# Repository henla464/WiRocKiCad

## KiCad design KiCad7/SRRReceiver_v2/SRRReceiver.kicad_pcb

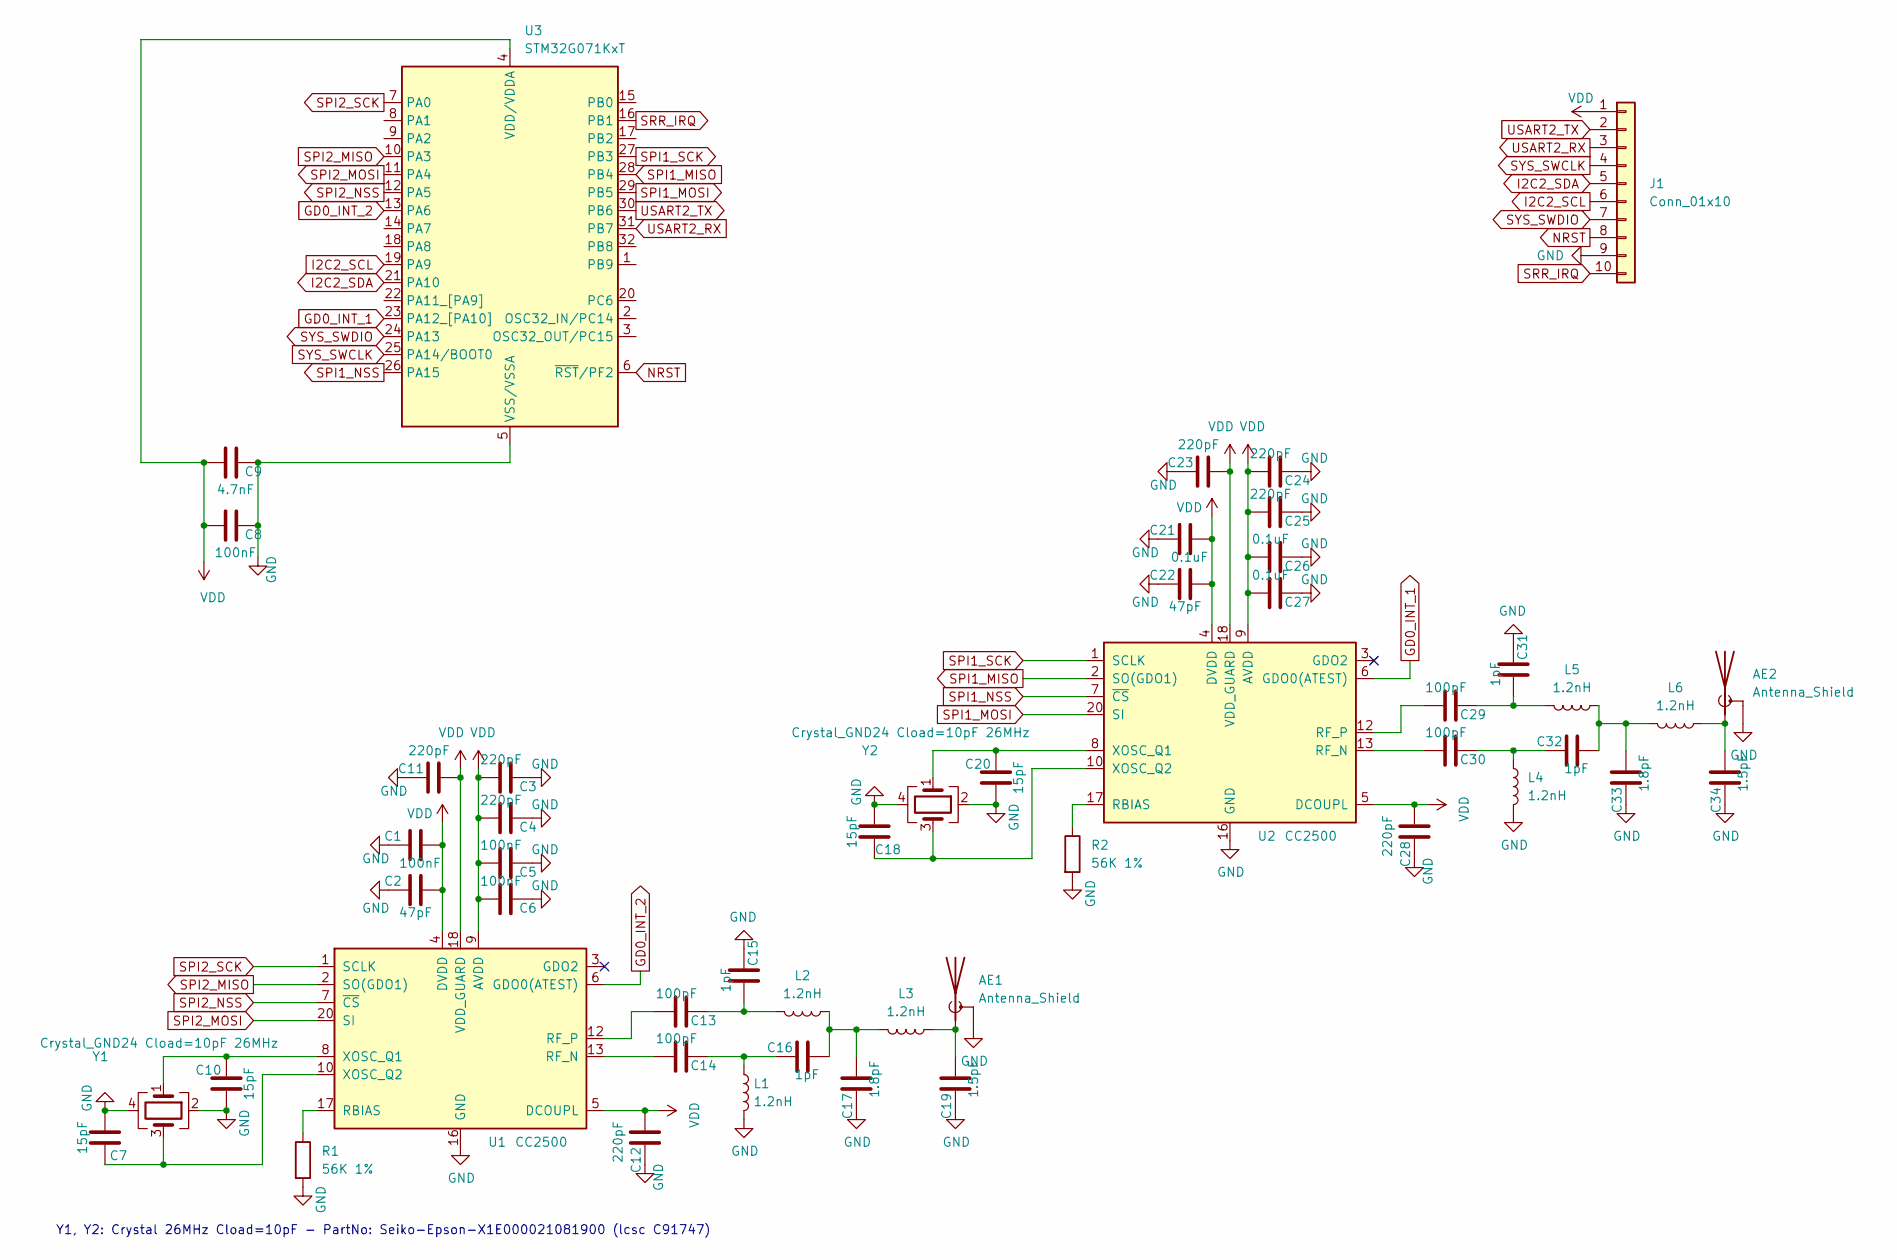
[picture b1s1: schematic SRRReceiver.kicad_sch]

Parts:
AE1, AE2: Antenna_Shield; Texas_SWRA117D_2.4GHz_Right
C1, C5, C6, C8: 100nF; C_0402_1005Metric; LCSC C1525
C2, C22: 47pF; C_0402_1005Metric; LCSC C1567
C3, C4, C11, C12, C23, C24, C25, C28: 220pF; C_0402_1005Metric; LCSC C16772
C7, C10, C18, C20: 15pF; C_0402_1005Metric; LCSC C1548
C9: 4.7nF; C_0402_1005Metric; LCSC C1538
C13, C14, C29, C30: 100pF; C_0402_1005Metric; LCSC C1546
C15, C16, C31, C32: 1pF; C_0402_1005Metric; LCSC C1550
C17, C33: 1.8pF; C_0402_1005Metric; LCSC C76902
C19, C34: 1.5pF; C_0402_1005Metric; LCSC C282238
C21, C26, C27: 0.1uF; C_0402_1005Metric; LCSC C1525
J1: Conn_01x10; FPC-Connector_1x10-1MP_P0.5mm_Horizontal
L1, L2, L3, L4, L5, L6: 1.2nH; L_0402_1005Metric; LCSC C77117
R1, R2: 56K 1%; R_0402_1005Metric; LCSC C25796
U1, U2: CC2500; Texas_S-PVQFN-N20_EP2.4x2.4mm; LCSC C57494
U3: STM32G071KxT; LQFP-32_7x7mm_P0.8mm
Y1, Y2: Crystal_GND24 Cload=10pF 26MHz; Crystal_SMD_3225-4Pin_3.2x2.5mm; LCSC C91747

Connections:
GD0_INT_1: U2.6 (GDO0(ATEST)), U3.23 (PA12_[PA10])
GD0_INT_2: U1.6 (GDO0(ATEST)), U3.13 (PA6)
GND: AE1.2 (Shield), AE2.2 (Shield), C1.1, C2.1, C3.1, C4.1, C5.1, C6.1, C7.1, C8.1, C9.1, C10.1, C11.1, C12.1, C15.1, C17.1, C18.1, C19.1, C20.1, C21.1, C22.1, C23.1, C24.1, C25.1, C26.1, C27.1, C28.1, C31.1, C33.1, C34.1, J1.9, L1.2, L4.2, R1.2, R2.2, U1.16 (GND), U1.19 (GND), U1.21 (GND), U2.16 (GND), U2.19 (GND), U2.21 (GND), U3.5 (VSS/VSSA), Y1.2, Y1.4, Y2.2, Y2.4
I2C2_SCL: J1.6, U3.19 (PA9)
I2C2_SDA: J1.5, U3.21 (PA10)
NRST: J1.8, U3.6 (~RST/PF2)
unnamed: AE1.1 (A), C19.2, L3.1
unnamed: AE2.1 (A), C34.2, L6.1
unnamed: C13.1, C15.2, L2.2
unnamed: C14.1, C16.1, L1.1
unnamed: C16.2, C17.2, L2.1, L3.2
unnamed: C29.1, C31.2, L5.2
unnamed: C30.1, C32.1, L4.1
unnamed: C32.2, C33.2, L5.1, L6.2
unnamed: R1.1, U1.17 (RBIAS)
unnamed: C14.2, U1.13 (RF_N)
unnamed: C13.2, U1.12 (RF_P)
unnamed: C10.2, U1.8 (XOSC_Q1), Y1.1
unnamed: C7.2, U1.10 (XOSC_Q2), Y1.3
unnamed: R2.1, U2.17 (RBIAS)
unnamed: C30.2, U2.13 (RF_N)
unnamed: C29.2, U2.12 (RF_P)
unnamed: C20.2, U2.8 (XOSC_Q1), Y2.1
unnamed: C18.2, U2.10 (XOSC_Q2), Y2.3
SPI1_MISO: U2.2 (SO(GDO1)), U3.28 (PB4)
SPI1_MOSI: U2.20 (SI), U3.29 (PB5)
SPI1_NSS: U2.7 (~CS), U3.26 (PA15)
SPI1_SCK: U2.1 (SCLK), U3.27 (PB3)
SPI2_MISO: U1.2 (SO(GDO1)), U3.10 (PA3)
SPI2_MOSI: U1.20 (SI), U3.11 (PA4)
SPI2_NSS: U1.7 (~CS), U3.12 (PA5)
SPI2_SCK: U1.1 (SCLK), U3.7 (PA0)
SRR_IRQ: J1.10, U3.16 (PB1)
SYS_SWCLK: J1.4, U3.25 (PA14/BOOT0)
SYS_SWDIO: J1.7, U3.24 (PA13)
USART2_RX: J1.3, U3.31 (PB7)
USART2_TX: J1.2, U3.30 (PB6)
VDD: C1.2, C2.2, C3.2, C4.2, C5.2, C6.2, C8.2, C9.2, C11.2, C12.2, C21.2, C22.2, C23.2, C24.2, C25.2, C26.2, C27.2, C28.2, J1.1, U1.4 (DVDD), U1.5 (DCOUPL), U1.9 (AVDD), U1.11 (AVDD), U1.14 (AVDD), U1.15 (AVDD), U1.18 (VDD_GUARD), U2.4 (DVDD), U2.5 (DCOUPL), U2.9 (AVDD), U2.11 (AVDD), U2.14 (AVDD), U2.15 (AVDD), U2.18 (VDD_GUARD), U3.4 (VDD/VDDA)

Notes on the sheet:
Y1, Y2: Crystal 26MHz Cload=10pF - PartNo: Seiko-Epson-X1E000021081900 (lcsc C91747)

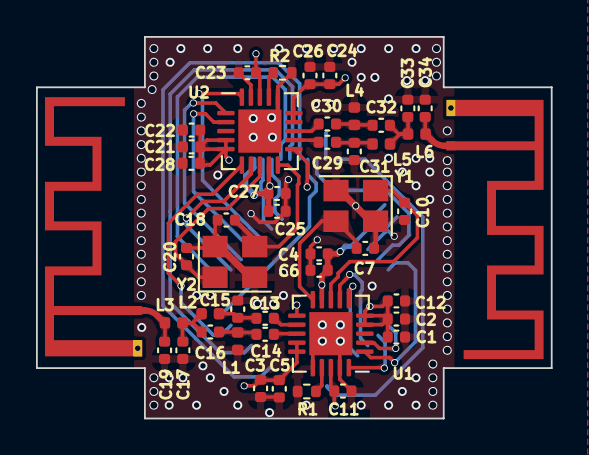
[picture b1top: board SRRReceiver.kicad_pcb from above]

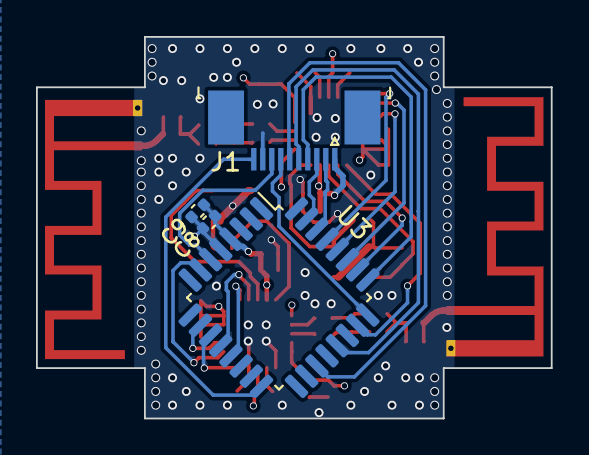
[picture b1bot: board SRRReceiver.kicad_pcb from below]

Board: 4 copper layers, 28.6 x 21.2 mm, 50 parts (4 on the bottom side), 38 nets.

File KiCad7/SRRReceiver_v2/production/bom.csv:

Designator,Footprint,Quantity,Value,LCSC Part #
"C1, C5, C6, C8",0402,4,100nF,C1525
"C10, C18, C20, C7",0402,4,15pF,C1548
"C11, C12, C23, C24, C25, C28, C3, C4",0402,8,220pF,C16772
"C13, C14, C29, C30",0402,4,100pF,C1546
"C15, C16, C31, C32",0402,4,1pF,C1550
"C17, C33",0402,2,1.8pF,C76902
"C19, C34",0402,2,1.5pF,C282238
"C2, C22",0402,2,47pF,C1567
"C21, C26, C27",0402,3,0.1uF,C1525
C9,0402,1,4.7nF,C1538
"L1, L2, L3, L4, L5, L6",0402,6,1.2nH,C77117
"R1, R2",0402,2,56K 1%,C25796
"U1, U2",Texas_S-PVQFN-N20_EP2.4x2.4mm,2,CC2500,C57494
"Y1, Y2",Crystal_SMD_3225-4Pin_3.2x2.5mm,2,Crystal_GND24 Cload=10pF 26MHz,C91747

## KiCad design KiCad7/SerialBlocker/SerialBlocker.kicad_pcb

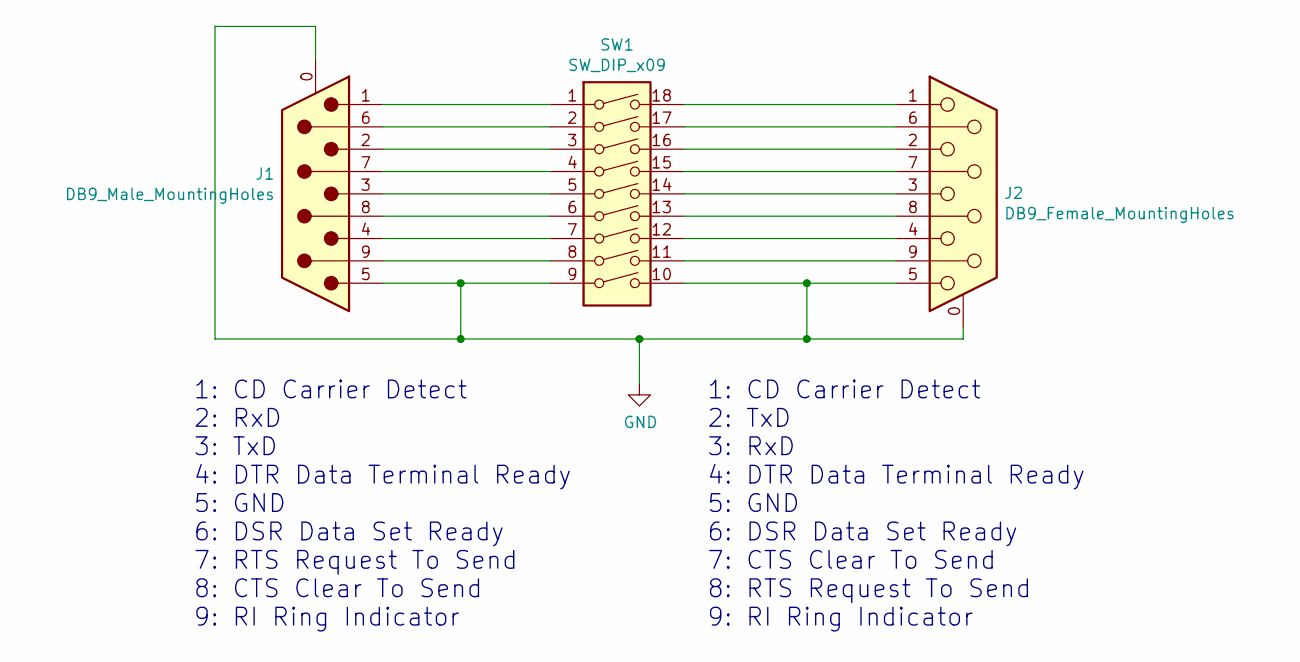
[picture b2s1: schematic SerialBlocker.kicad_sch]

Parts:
J1: DB9_Male_MountingHoles; DSUB-9_Male_Horizontal_P2.77x2.84mm_Edge_Housed_MountingHol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
J2: DB9_Female_MountingHoles; DSUB-9_Female_Horizontal_P2.77x2.84mm_Edge_offset6.96mm_cen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
SW1: SW_DIP_x09; PinHeader_Serial_Blocker

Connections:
GND: J1.0 (PAD), J1.5, J2.0 (PAD), J2.5, SW1.9, SW1.10
unnamed: J1.1, SW1.1
unnamed: J1.2, SW1.3
unnamed: J1.3, SW1.5
unnamed: J1.4, SW1.7
unnamed: J1.6, SW1.2
unnamed: J1.7, SW1.4
unnamed: J1.8, SW1.6
unnamed: J1.9, SW1.8
unnamed: J2.1, SW1.18
unnamed: J2.2, SW1.16
unnamed: J2.3, SW1.14
unnamed: J2.4, SW1.12
unnamed: J2.6, SW1.17
unnamed: J2.7, SW1.15
unnamed: J2.8, SW1.13
unnamed: J2.9, SW1.11

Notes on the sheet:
1: CD Carrier Detect 2: RxD 3: TxD 4: DTR Data Terminal Ready 5: GND 6: DSR Data Set Ready 7: RTS Request To Send 8: CTS Clear To Send 9: RI Ring Indicator
1: CD Carrier Detect 2: TxD 3: RxD 4: DTR Data Terminal Ready 5: GND 6: DSR Data Set Ready 7: CTS Clear To Send 8: RTS Request To Send 9: RI Ring Indicator

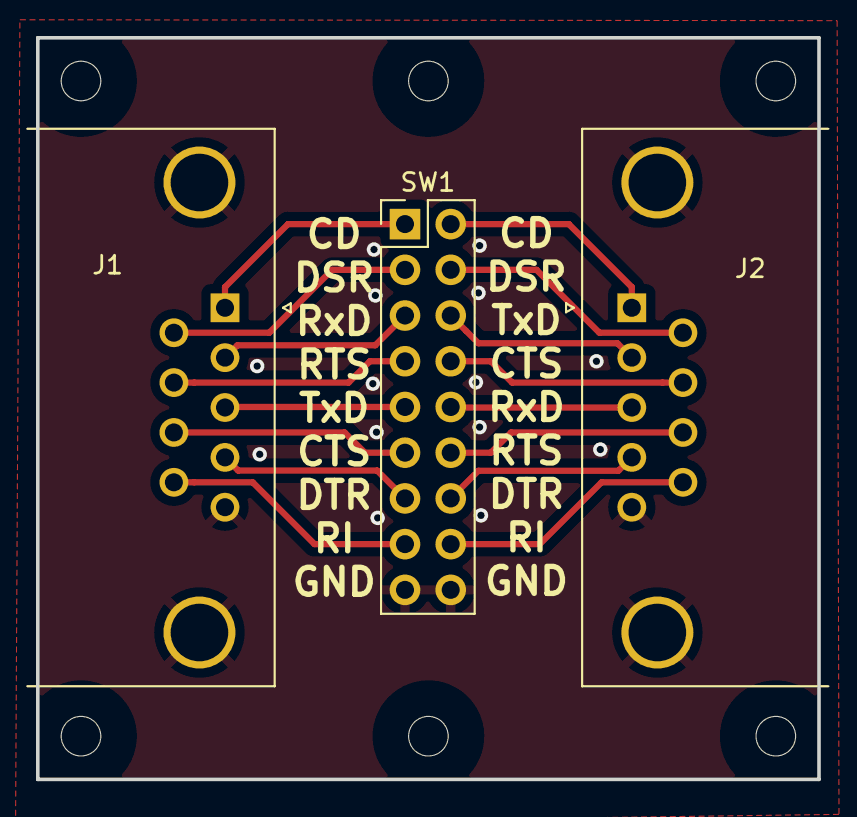
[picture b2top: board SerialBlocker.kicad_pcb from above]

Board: 2 copper layers, 43.4 x 41.2 mm, 3 parts (0 on the bottom side), 17 nets.

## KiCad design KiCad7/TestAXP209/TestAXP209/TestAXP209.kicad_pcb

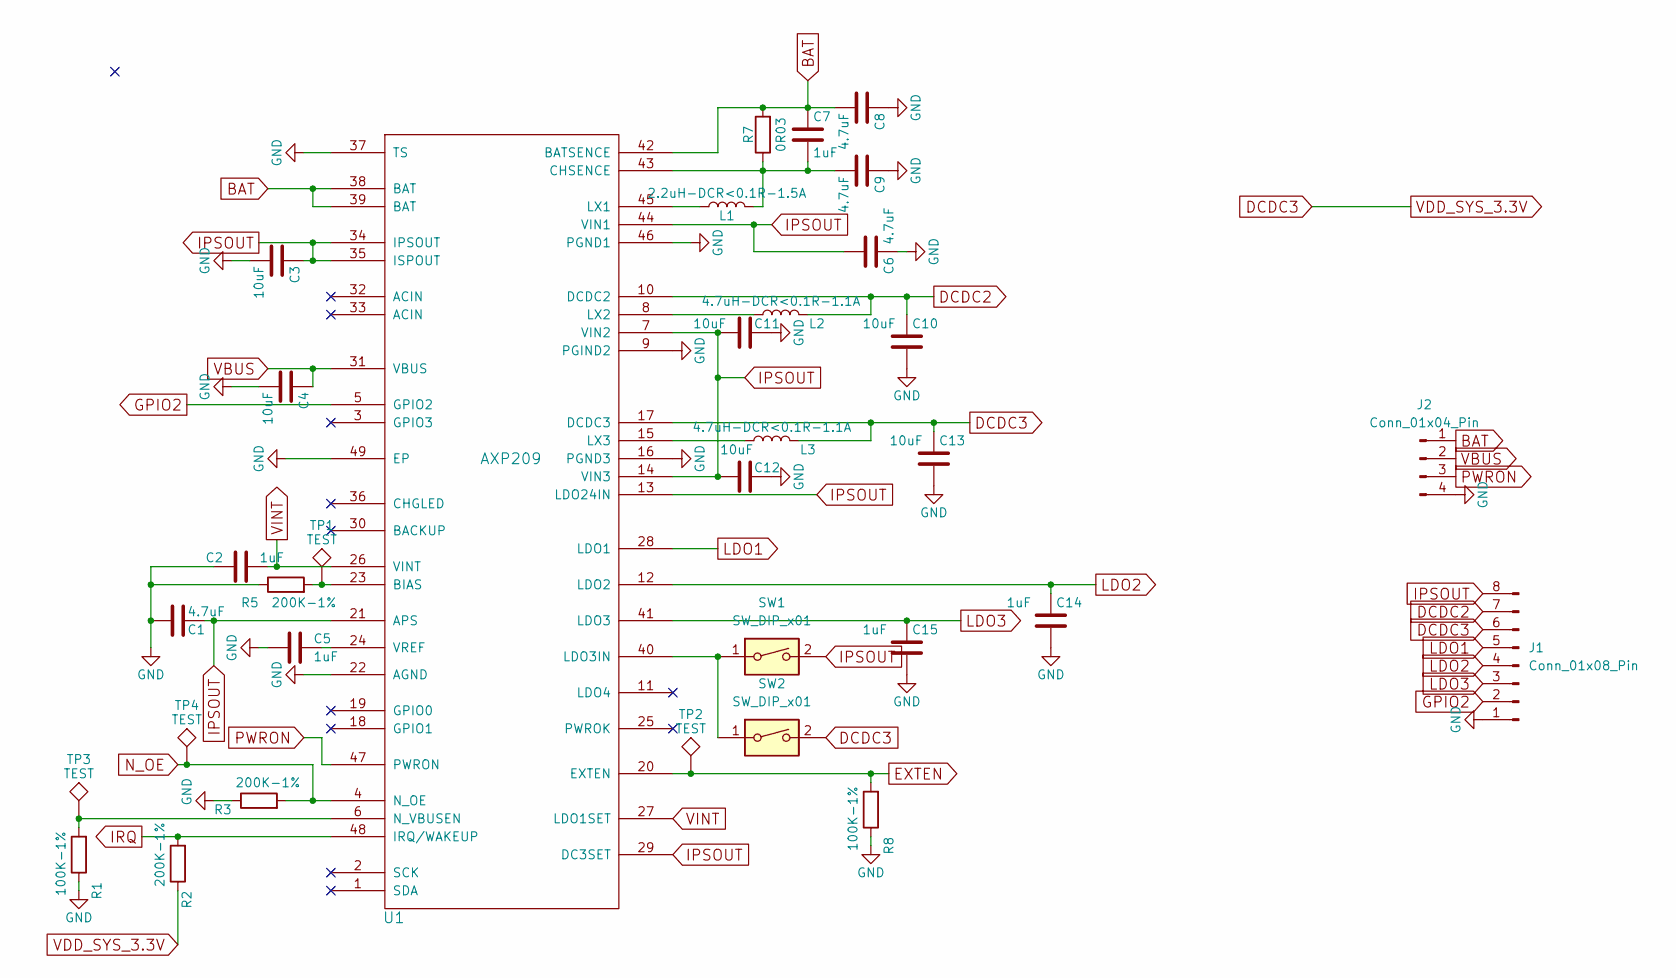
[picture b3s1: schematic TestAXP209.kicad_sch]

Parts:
C1, C6, C8, C9: 4.7uF; C_0603_1608Metric; ManufacturerPartNumber CL10A475KO8NNNC; LCSC Part # C19666
C2, C5, C7: 1uF; C_0603_1608Metric; ManufacturerPartNumber CL10A105KB8NNNC; LCSC Part # C15849
C3, C4: 10uF; C_0603_1608Metric; ManufacturerPartNumber CL10A106KP8NNNC; LCSC Part # C19702
C10, C11, C12, C13: 10uF; C_0603_1608Metric; ManufacturerPartNumber CL10A475KO8NNNC; LCSC Part # C19666
C14, C15: 1uF; C_0603_1608Metric; ManufacturerPartNumber CL10A475KO8NNNC; LCSC Part # C19666
J1: Conn_01x08_Pin; PinHeader_1x08_P2.54mm_Vertical
J2: Conn_01x04_Pin; PinHeader_1x04_P2.54mm_Vertical
L1: 2.2uH-DCR<0.1R-1.5A; Inductor_SLW4018; ManufacturerPartNumber SLW4018S2R2MST; LCSC Part # C206341
L2: 4.7uH-DCR<0.1R-1.1A; Inductor_SLW4018; ManufacturerPartNumber ?? DFE322520FD-4R7M=P2; LCSC Part # ?? C2045343
L3: 4.7uH-DCR<0.1R-1.1A; Inductor_SLW4018; ManufacturerPartNumber SWPA4030S4R7MT; LCSC Part # C57269
R1, R8: 100K-1%; R_0603_1608Metric; ManufacturerPartNumber 0603WAF1003T5E; LCSC Part # C25803
R2, R3, R5: 200K-1%; R_0603_1608Metric; ManufacturerPartNumber 0603WAF2003T5E; LCSC Part # C25811
R7: 0R03; R_0805_2012Metric; ManufacturerPartNumber 0805W4F300MT5E; LCSC Part # C247605
SW1, SW2: SW_DIP_x01; PinHeader_1x02_P2.54mm_Vertical
TP1, TP2, TP3, TP4: TEST; TestPoint_Pad_D1.0mm
U1: AXP209; qfn48_6x6mm_Pitch0.4mm; ManufacturerPartNumber AXP209; LCSC Part # C2997895

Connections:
BAT: C7.1, C8.2, J2.1, R7.2, U1.38 (BAT), U1.39 (BAT), U1.42 (BATSENCE)
DCDC2: C10.1, J1.7, L2.2, U1.10 (DCDC2)
DCDC3: C13.1, J1.6, L3.2, R2.1, SW2.2, U1.17 (DCDC3)
EXTEN: R8.2, TP2.1, U1.20 (EXTEN)
GND: C1.2, C2.2, C3.2, C4.2, C5.2, C6.1, C8.1, C9.1, C10.2, C11.2, C12.2, C13.2, C14.2, C15.2, J1.1, J2.4, R1.1, R3.1, R5.1, R8.1, U1.9 (PGIND2), U1.16 (PGND3), U1.22 (AGND), U1.37 (TS), U1.46 (PGND1), U1.49 (EP)
GPIO2: J1.2, U1.5 (GPIO2)
IPSOUT: C1.1, C3.1, C6.2, C11.1, C12.1, J1.8, SW1.2, U1.7 (VIN2), U1.13 (LDO24IN), U1.14 (VIN3), U1.21 (APS), U1.29 (DC3SET), U1.34 (IPSOUT), U1.35 (ISPOUT), U1.44 (VIN1)
IRQ: R2.2, U1.48 (IRQ/WAKEUP)
LDO1: J1.5, U1.28 (LDO1)
LDO2: C14.1, J1.4, U1.12 (LDO2)
LDO3: C15.1, J1.3, U1.41 (LDO3)
N_OE: R3.2, TP4.1, U1.4 (N_OE)
unnamed: R5.2, TP1.1, U1.23 (BIAS)
unnamed: C7.2, C9.2, L1.2, R7.1, U1.43 (CHSENCE)
unnamed: SW1.1, SW2.1, U1.40 (LDO3IN)
unnamed: L1.1, U1.45 (LX1)
unnamed: L2.1, U1.8 (LX2)
unnamed: L3.1, U1.15 (LX3)
unnamed: R1.2, TP3.1, U1.6 (N_VBUSEN)
unnamed: C5.1, U1.24 (VREF)
PWRON: J2.3, U1.47 (PWRON)
VBUS: C4.1, J2.2, U1.31 (VBUS)
VINT: C2.1, U1.26 (VINT), U1.27 (LDO1SET)

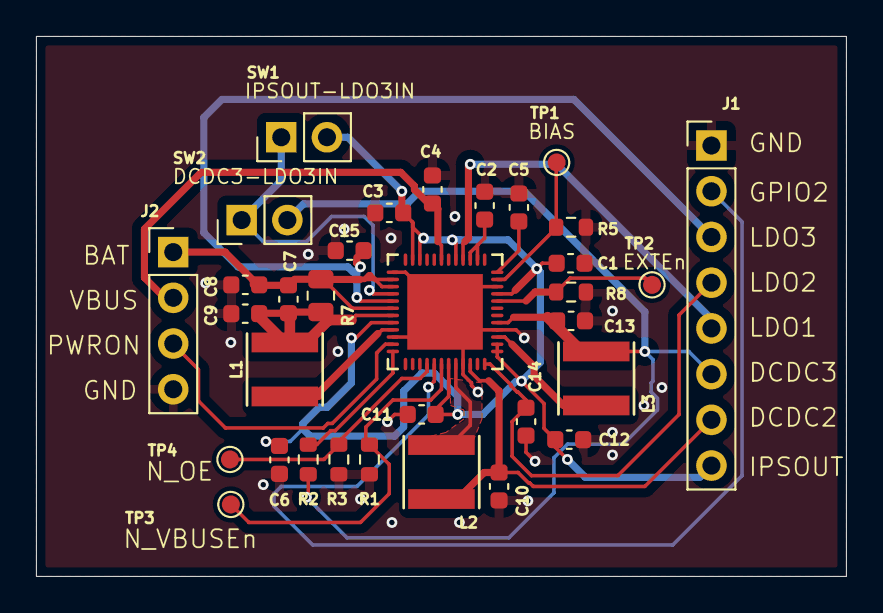
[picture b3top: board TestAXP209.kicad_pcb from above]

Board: 2 copper layers, 45.0 x 30.0 mm, 33 parts (0 on the bottom side), 23 nets.

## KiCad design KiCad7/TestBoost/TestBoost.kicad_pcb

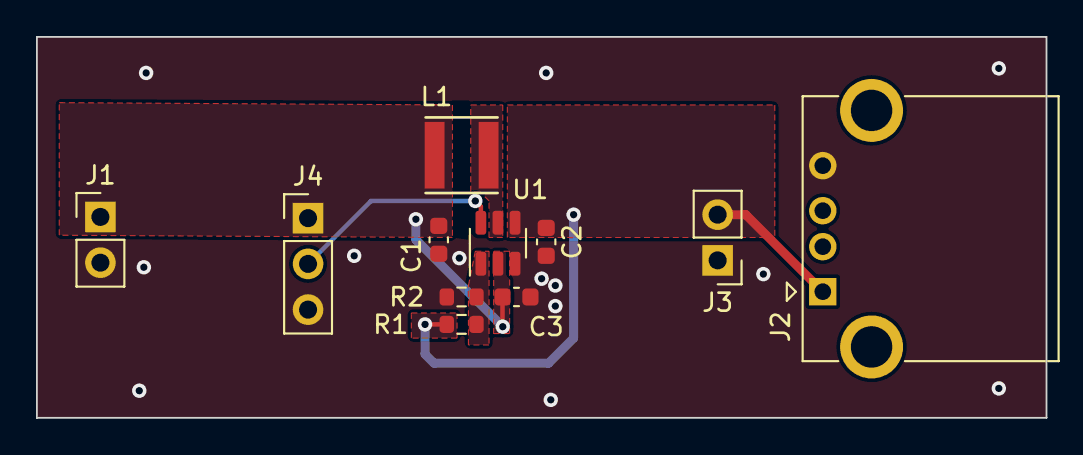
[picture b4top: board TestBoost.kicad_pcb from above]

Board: 2 copper layers, 56.1 x 21.2 mm, 11 parts (0 on the bottom side), 6 nets.

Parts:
C1, C2: 22uF; C_0603_1608Metric
C3: C; C_0603_1608Metric
J1, J3: Conn_01x02_Male; PinHeader_1x02_P2.54mm_Vertical
J2: USB_A; USB_A_CONNFLY_DS1095-WNR0
J4: Conn_01x03_Male; PinHeader_1x03_P2.54mm_Vertical
L1: 1.5uH; Inductor_SLW4018
R1: 500kOhm; R_0603_1608Metric
R2: 150kOhm; R_0603_1608Metric
U1: TSOT-23-6

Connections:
/Vin: C1.1, C3.1, J1.1, J4.1, L1.1, U1.2 (IN)
/Vout: C2.1, J2.1 (VBUS), J3.2, R1.1, U1.4 (OUT)
GND: C1.2, C2.2, C3.2, J1.2, J2.4 (GND), J3.1, J4.3, R2.2, U1.3 (GND)
unnamed: J4.2, U1.6 (EN)
unnamed: R1.2, R2.1, U1.1 (FB)
unnamed: L1.2, U1.5 (LX)

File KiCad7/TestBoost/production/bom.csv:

Designator,Footprint,Quantity,Value,LCSC Part #
"C1, C2",0603,2,22uF,
C3,0603,1,C,
"J1, J3",PinHeader_1x02_P2.54mm_Vertical,2,Conn_01x02_Male,
J2,USB_A_CONNFLY_DS1095-WNR0,1,USB_A,
J4,PinHeader_1x03_P2.54mm_Vertical,1,Conn_01x03_Male,
L1,Inductor_SLW4018,1,1.5uH,
R1,0603,1,500kOhm,
R2,0603,1,150kOhm,
U1,TSOT-23-6,1,~,

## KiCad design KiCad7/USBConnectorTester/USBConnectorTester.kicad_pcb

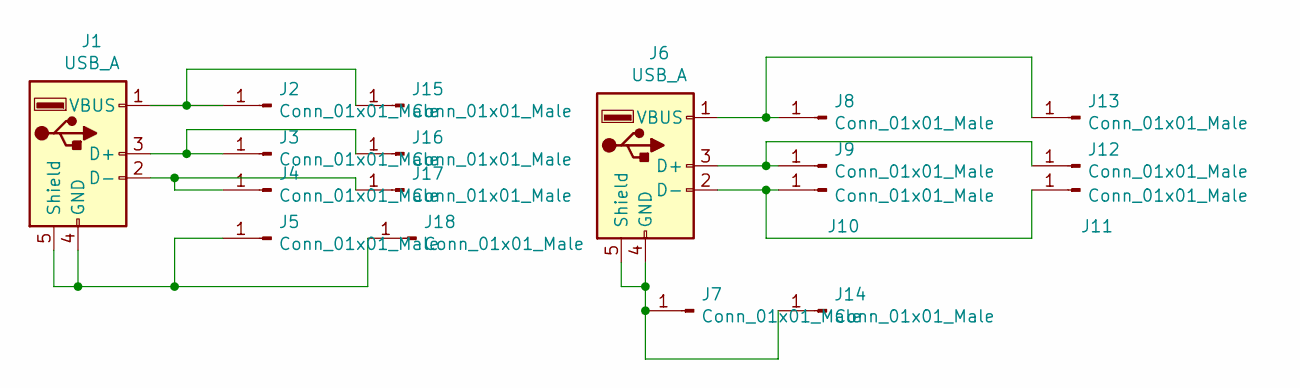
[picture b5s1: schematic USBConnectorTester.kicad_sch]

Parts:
J1: USB_A; USBA-Male-through-hole-C112454
J2, J3, J4, J5, J7, J8, J9, J10: Conn_01x01_Male; PinHeader_1x01_P2.54mm_Vertical
J6: USB_A; USB_A_CONNFLY_DS1095-WNR0
J11, J12, J13, J14, J15, J16, J17, J18: Conn_01x01_Male; RoundPadThroughHole

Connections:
unnamed: J1.3 (D+), J3.1, J16.1
unnamed: J1.2 (D-), J4.1, J17.1
unnamed: J1.4 (GND), J1.5 (Shield), J5.1, J18.1
unnamed: J1.1 (VBUS), J2.1, J15.1
unnamed: J6.2 (D-), J10.1, J11.1
unnamed: J6.3 (D+), J9.1, J12.1
unnamed: J6.1 (VBUS), J8.1, J13.1
unnamed: J6.4 (GND), J6.5 (Shield), J7.1, J14.1

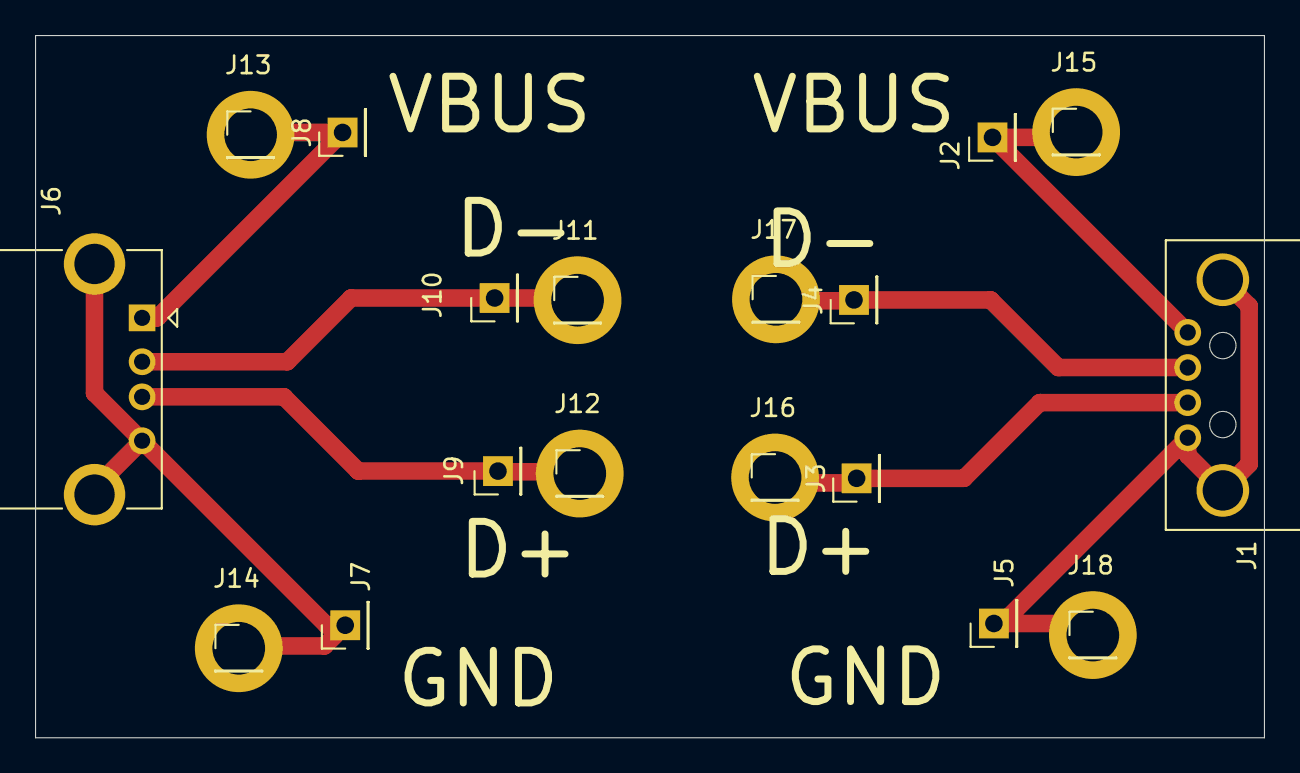
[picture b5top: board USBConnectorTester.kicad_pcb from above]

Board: 2 copper layers, 70.0 x 40.0 mm, 18 parts (0 on the bottom side), 8 nets.
